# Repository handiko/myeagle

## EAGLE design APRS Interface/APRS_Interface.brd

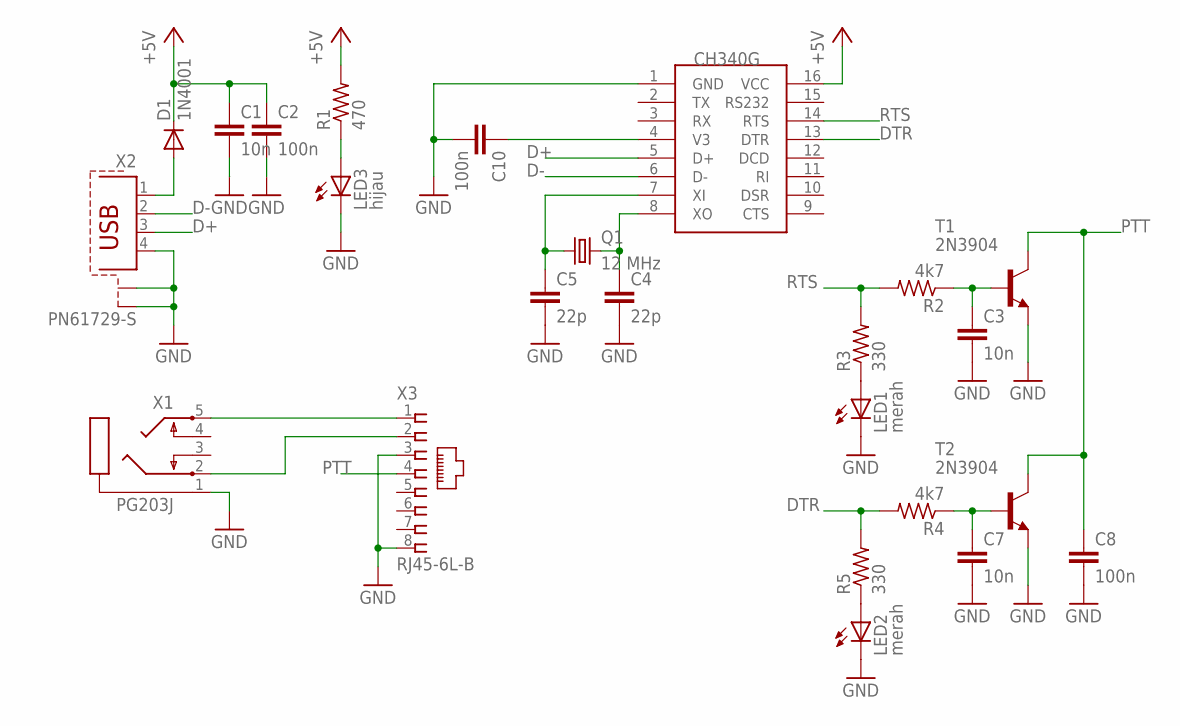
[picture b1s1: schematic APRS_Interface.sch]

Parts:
C1, C3, C7: 10n; C0805K
C2, C8, C10: 100n; C0805K
C4, C5: 22p; C0805K
D1: 1N4001; DO35-7
LED1, LED2: merah; LED3MM
LED3: hijau; LED3MM
Q1: 12 MHz; HC49/S
R1: 470; R0805
R2, R4: 4k7; R0805
R3, R5: 330; R0805
T1, T2: 2N3904; TO92-EBC
U$1: CH340G; SOIC16
X1: PG203J
X2: PN61729-S
X3: RJ45-6L-B; RJ45-NO-SHIELD

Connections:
+5V: C1.1, C2.1, D1.C, R1.2, U$1.16 (VCC)
D+: U$1.5 (D+), X2.3
D-: U$1.6 (D-), X2.2
DTR: R4.2, R5.2, U$1.13 (DTR)
GND: C1.2, C2.2, C3.2, C4.2, C5.2, C7.2, C8.2, C10.2, LED1.K (C), LED2.K (C), LED3.K (C), T1.E, T2.E, U$1.1 (GND), X1.1, X2.4, X2.S1, X2.S2, X3.3, X3.8
unnamed: D1.A, X2.1
unnamed: C4.1, Q1.2, U$1.8 (XO)
unnamed: C5.1, Q1.1, U$1.7 (XI)
unnamed: C10.1, U$1.4 (V3)
unnamed: C3.1, R2.1, T1.B
unnamed: X1.5, X3.1
unnamed: LED1.A, R3.1
unnamed: X1.2, X3.2
unnamed: C7.1, R4.1, T2.B
unnamed: LED3.A, R1.1
unnamed: LED2.A, R5.1
PTT: C8.1, T1.C, T2.C, X3.4
RTS: R2.2, R3.2, U$1.14 (RTS)

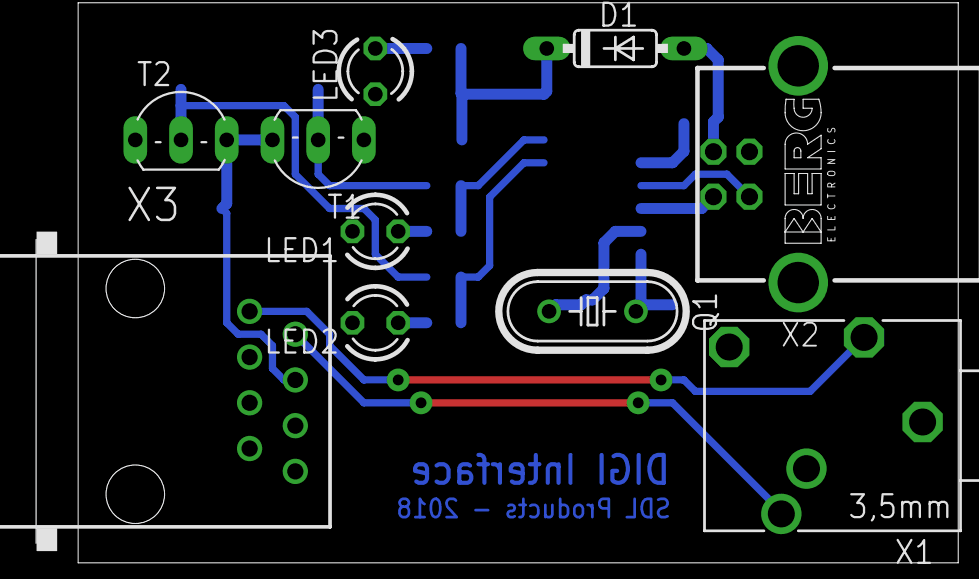
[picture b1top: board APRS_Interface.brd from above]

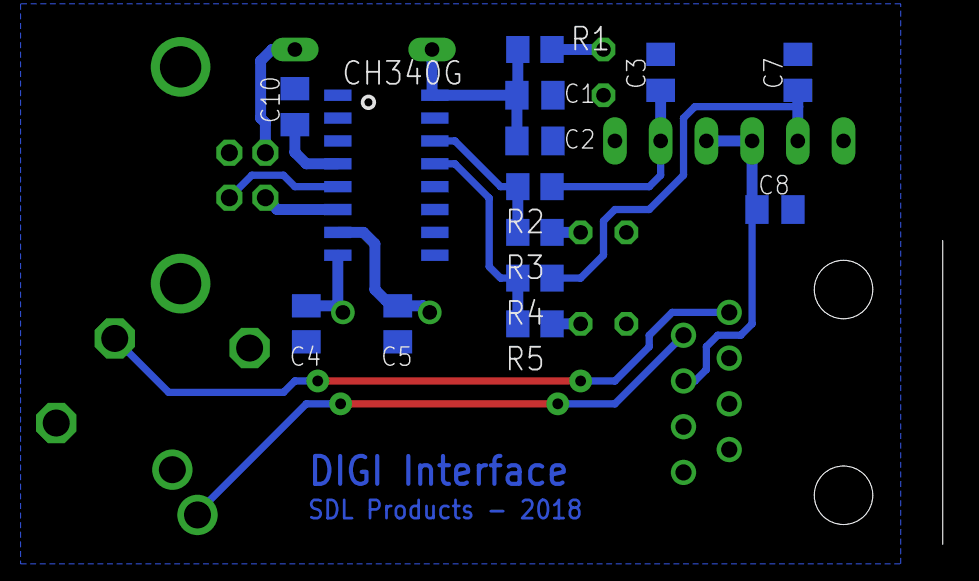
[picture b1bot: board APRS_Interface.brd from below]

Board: 2 copper layers, 24 parts (14 on the bottom side), 18 nets.

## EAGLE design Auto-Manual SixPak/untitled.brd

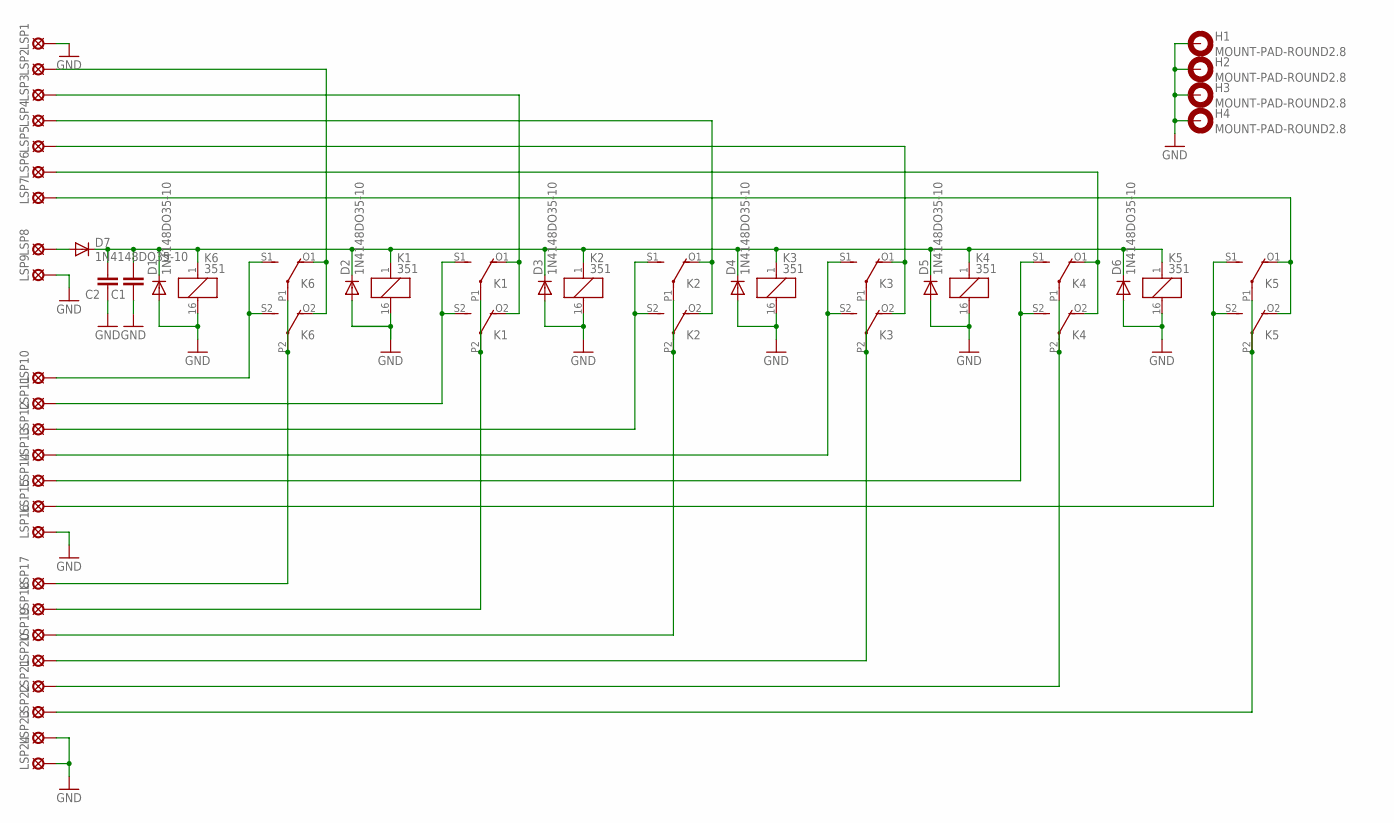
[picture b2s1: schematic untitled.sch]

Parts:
C1, C2: C-EU050-025X075; C050-025X075
D1, D2, D3, D4, D5, D6, D7: 1N4148DO35-10; DO35-10
H1, H2, H3, H4: MOUNT-PAD-ROUND2.8; 2,8-PAD
K1, K2, K3, K4, K5, K6: 351
LSP1, LSP2, LSP3, LSP4, LSP5, LSP6, LSP7, LSP8, LSP9, LSP10, LSP11, LSP12, LSP13, LSP14, LSP15, LSP16, LSP17, LSP18, LSP19, LSP20, LSP21, LSP22, LSP23, LSP24: SE14

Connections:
GND: C1.1, C2.1, D1.A, D2.A, D3.A, D4.A, D5.A, D6.A, H1.B2,8, H2.B2,8, H3.B2,8, H4.B2,8, K2.16 (2), K3.16 (2), K4.16 (2), K5.16 (2), K6.16 (2), LSP1.MP, LSP9.MP, LSP16.MP, LSP23.MP, LSP24.MP
GND1: K1.16 (2)
unnamed: K6.O1 (O), K6.O2 (O), LSP2.MP
unnamed: K6.S1 (S), K6.S2 (S), LSP10.MP
unnamed: K1.O1 (O), K1.O2 (O), LSP3.MP
unnamed: K1.S1 (S), K1.S2 (S), LSP11.MP
unnamed: K2.O1 (O), K2.O2 (O), LSP4.MP
unnamed: K2.S1 (S), K2.S2 (S), LSP12.MP
unnamed: K3.O1 (O), K3.O2 (O), LSP5.MP
unnamed: K3.S1 (S), K3.S2 (S), LSP13.MP
unnamed: K4.O1 (O), K4.O2 (O), LSP6.MP
unnamed: K4.S1 (S), K4.S2 (S), LSP14.MP
unnamed: K5.O1 (O), K5.O2 (O), LSP7.MP
unnamed: K5.S1 (S), K5.S2 (S), LSP15.MP
unnamed: K6.P1, K6.P2, LSP17.MP
unnamed: K1.P1, K1.P2, LSP18.MP
unnamed: K2.P1, K2.P2, LSP19.MP
unnamed: C1.2, C2.2, D1.C, D2.C, D3.C, D4.C, D5.C, D6.C, D7.C, K1.1, K2.1, K3.1, K4.1, K5.1, K6.1
unnamed: K3.P1, K3.P2, LSP20.MP
unnamed: K4.P1, K4.P2, LSP21.MP
unnamed: K5.P1, K5.P2, LSP22.MP
unnamed: D7.A, LSP8.MP

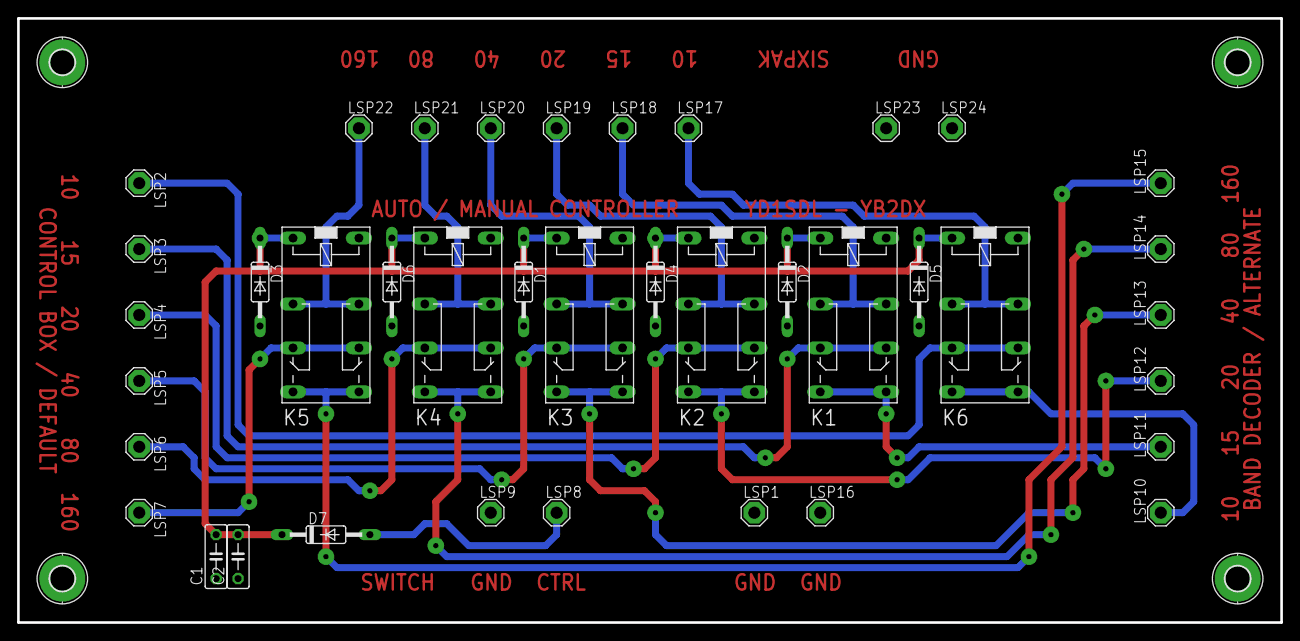
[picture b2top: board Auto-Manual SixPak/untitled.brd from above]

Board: 2 copper layers, 146.1 x 69.8 mm, 43 parts (0 on the bottom side), 21 nets.

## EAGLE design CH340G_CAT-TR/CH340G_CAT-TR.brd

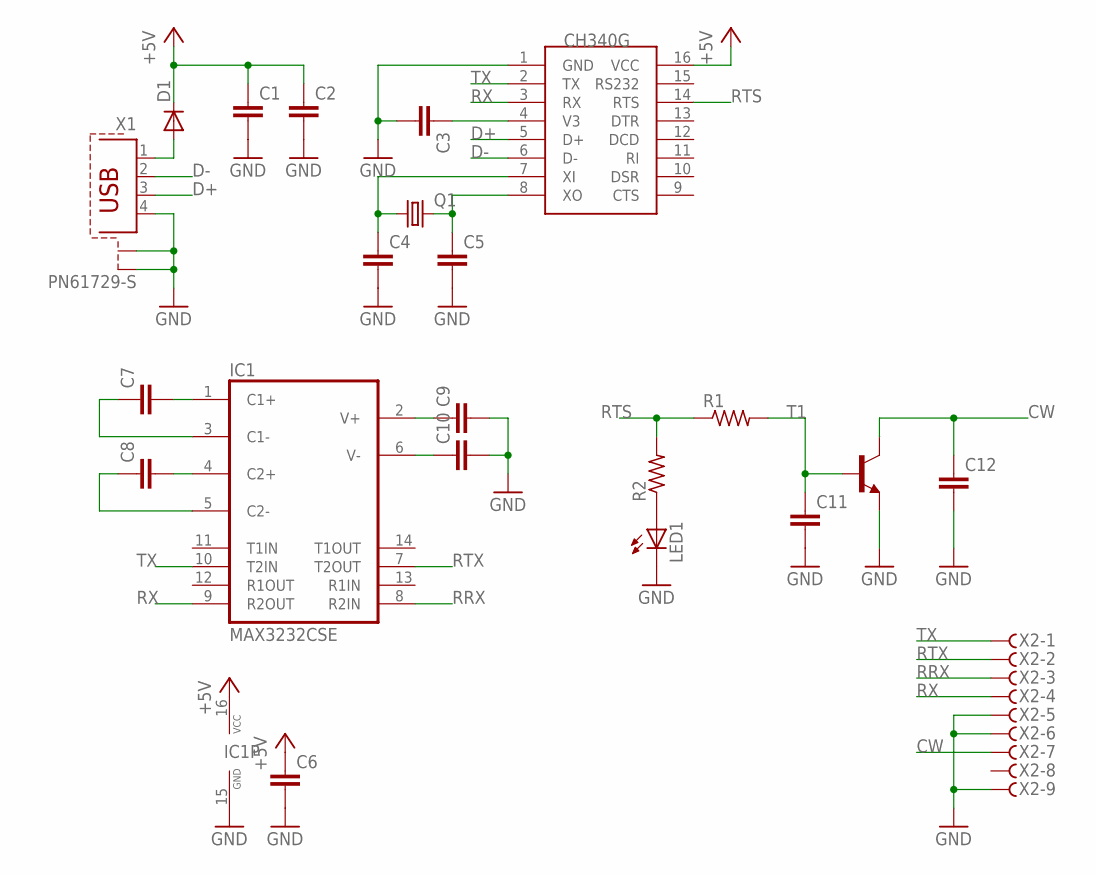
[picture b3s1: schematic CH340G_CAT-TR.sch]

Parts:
C1, C2, C3, C4, C5, C6, C7, C8, C9, C10, C11, C12: C-EUC0805K; C0805K
D1: 1N4148DO35-7; DO35-7
IC1: MAX3232CSE; SO16
LED1: LED3MM
Q1: CRYSTALHC49S; HC49/S
R1, R2: R-US_M0805; M0805
T1: BC548-NPN-TO92-CBE; TO92-CBE
U$1: CH340G; SOIC16
X1: PN61729-S
X2: F09HPS; F09HP

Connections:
+5V: C1.1, C2.1, C6.1, D1.C, IC1.16 (VCC), U$1.16 (VCC)
CW: C12.1, T1.C, X2.7
D+: U$1.5 (D+), X1.3
D-: U$1.6 (D-), X1.2
GND: C1.2, C2.2, C3.2, C4.2, C5.2, C6.2, C9.2, C10.2, C11.2, C12.2, IC1.15 (GND), LED1.K (C), T1.E, U$1.1 (GND), X1.4, X1.S1, X1.S2, X2.5, X2.6, X2.9
unnamed: D1.A, X1.1
unnamed: C4.1, Q1.1, U$1.7 (XI)
unnamed: C5.1, Q1.2, U$1.8 (XO)
unnamed: C10.1, IC1.6 (V-)
unnamed: C3.1, U$1.4 (V3)
unnamed: C9.1, IC1.2 (V+)
unnamed: C8.2, IC1.4 (C2+)
unnamed: C7.2, IC1.1 (C1+)
unnamed: C7.1, IC1.3 (C1-)
unnamed: C8.1, IC1.5 (C2-)
unnamed: C11.1, R1.2, T1.B
unnamed: LED1.A, R2.1
RRX: IC1.8 (R2IN), X2.3
RTS: R1.1, R2.2, U$1.14 (RTS)
RTX: IC1.7 (T2OUT), X2.2
RX: IC1.9 (R2OUT), U$1.3 (RX), X2.4
TX: IC1.10 (T2IN), U$1.2 (TX), X2.1

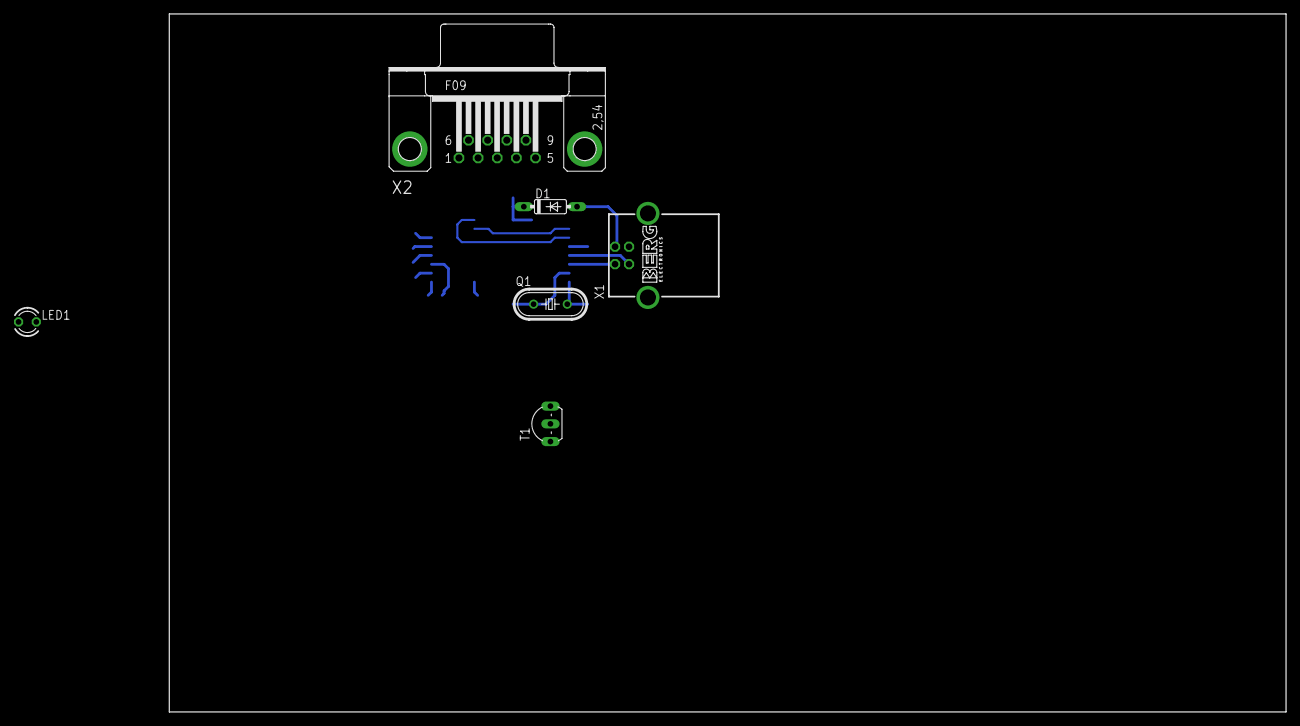
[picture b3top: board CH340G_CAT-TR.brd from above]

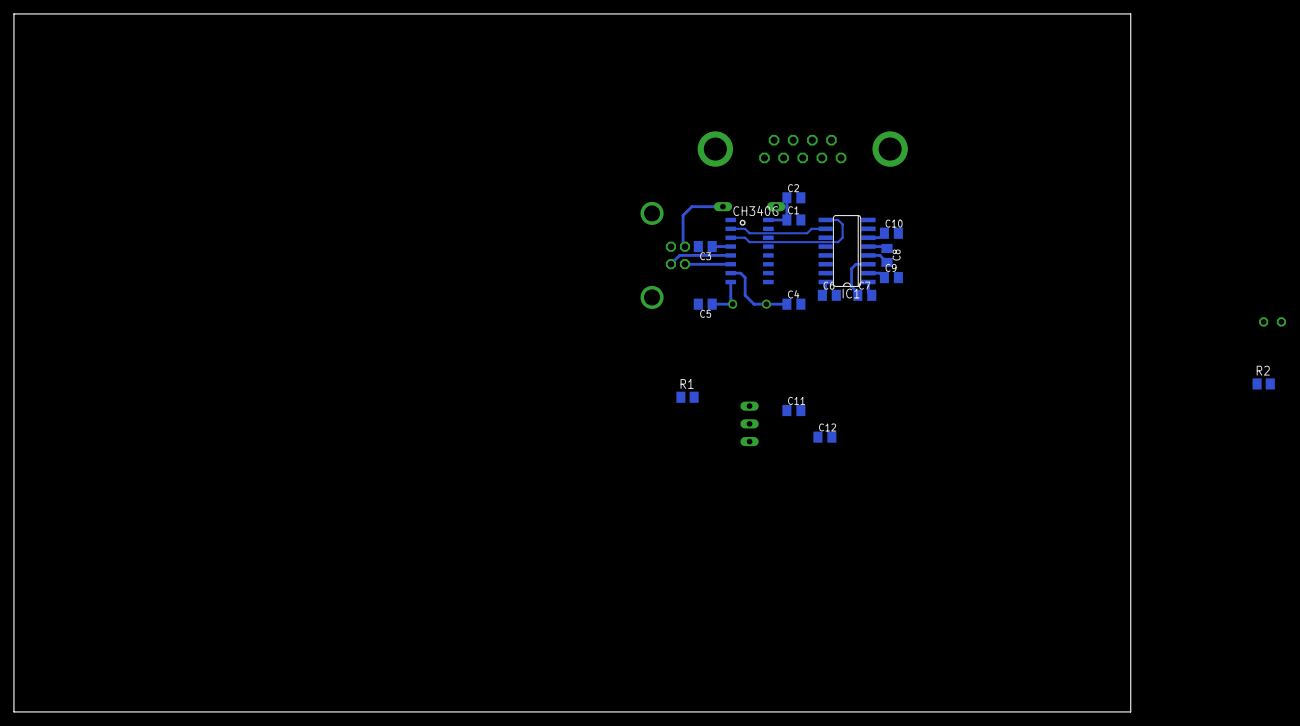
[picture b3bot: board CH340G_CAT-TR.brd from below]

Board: 2 copper layers, 160.0 x 100.0 mm, 22 parts (16 on the bottom side), 22 nets.

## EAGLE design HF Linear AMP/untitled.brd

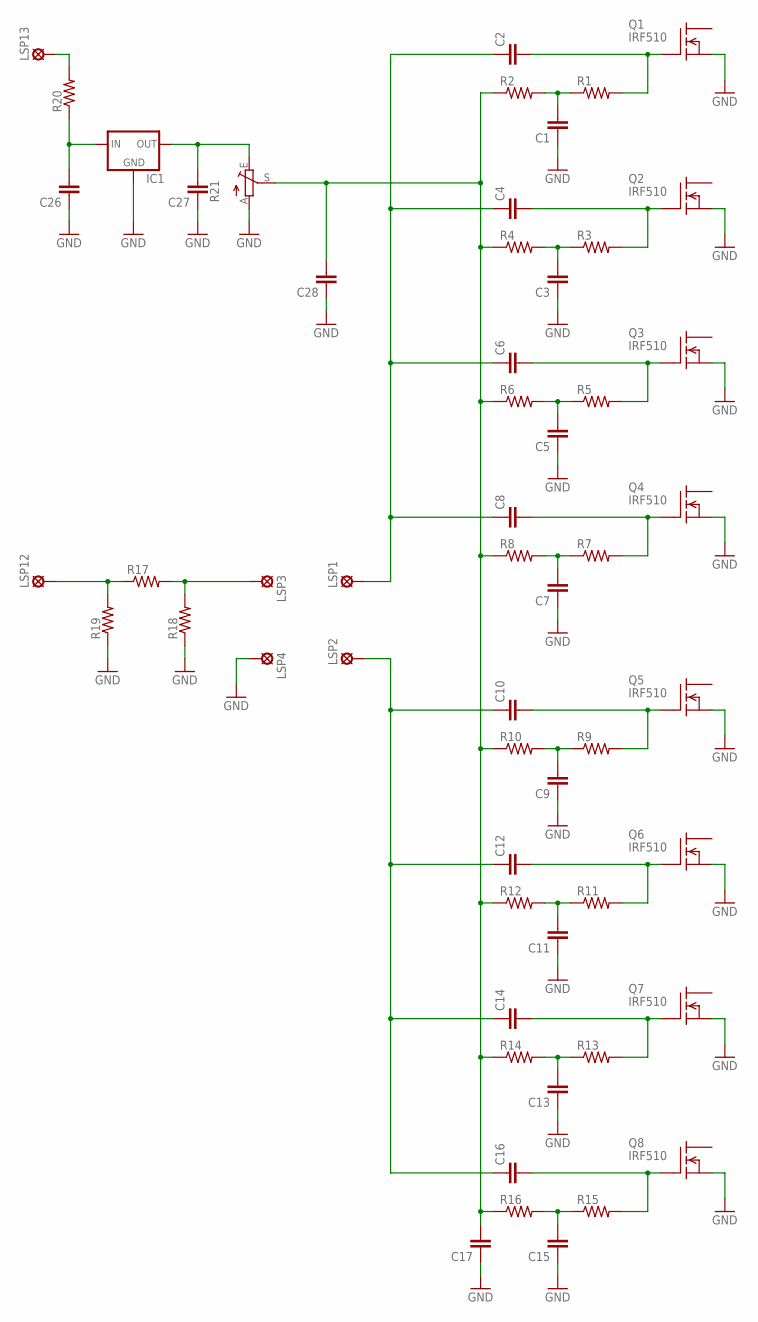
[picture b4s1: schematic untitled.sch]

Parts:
C1, C2, C3, C4, C5, C6, C7, C8, C9, C10, C11, C12, C13, C14, C15, C16, C17, C26, C27, C28: C-EU075-032X103; C075-032X103
IC1: 78XXS
LSP1, LSP2, LSP3, LSP4, LSP12, LSP13: SE14
Q1, Q2, Q3, Q4, Q5, Q6, Q7, Q8: IRF510; TO220
R1, R2, R3, R4, R5, R6, R7, R8, R9, R10, R11, R12, R13, R14, R15, R16, R17, R18, R19, R20: R-US_0309/12; 0309/12
R21: TRIM_EU-CA6V; CA6V

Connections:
GND: C1.1, C3.1, C5.1, C7.1, C9.1, C11.1, C13.1, C15.1, C17.1, C26.1, C27.1, C28.1, IC1.GND, LSP4.MP, Q1.3 (S), Q2.3 (S), Q3.3 (S), Q4.3 (S), Q5.3 (S), Q6.3 (S), Q7.3 (S), Q8.3 (S), R18.1, R19.1, R21.A
unnamed: C2.2, Q1.1 (G), R1.2
unnamed: C1.2, R1.1, R2.2
unnamed: C4.2, Q2.1 (G), R3.2
unnamed: C3.2, R3.1, R4.2
unnamed: C6.2, Q3.1 (G), R5.2
unnamed: C5.2, R5.1, R6.2
unnamed: C8.2, Q4.1 (G), R7.2
unnamed: C7.2, R7.1, R8.2
unnamed: C10.2, Q5.1 (G), R9.2
unnamed: C9.2, R9.1, R10.2
unnamed: C12.2, Q6.1 (G), R11.2
unnamed: C11.2, R11.1, R12.2
unnamed: C14.2, Q7.1 (G), R13.2
unnamed: C13.2, R13.1, R14.2
unnamed: C16.2, Q8.1 (G), R15.2
unnamed: C15.2, R15.1, R16.2
unnamed: C17.2, C28.2, R2.1, R4.1, R6.1, R8.1, R10.1, R12.1, R14.1, R16.1, R21.S
unnamed: C10.1, C12.1, C14.1, C16.1, LSP2.MP
unnamed: C2.1, C4.1, C6.1, C8.1, LSP1.MP
unnamed: LSP3.MP, R17.2, R18.2
unnamed: LSP12.MP, R17.1, R19.2
unnamed: C26.2, IC1.IN, R20.1
unnamed: LSP13.MP, R20.2
unnamed: C27.2, IC1.OUT, R21.E

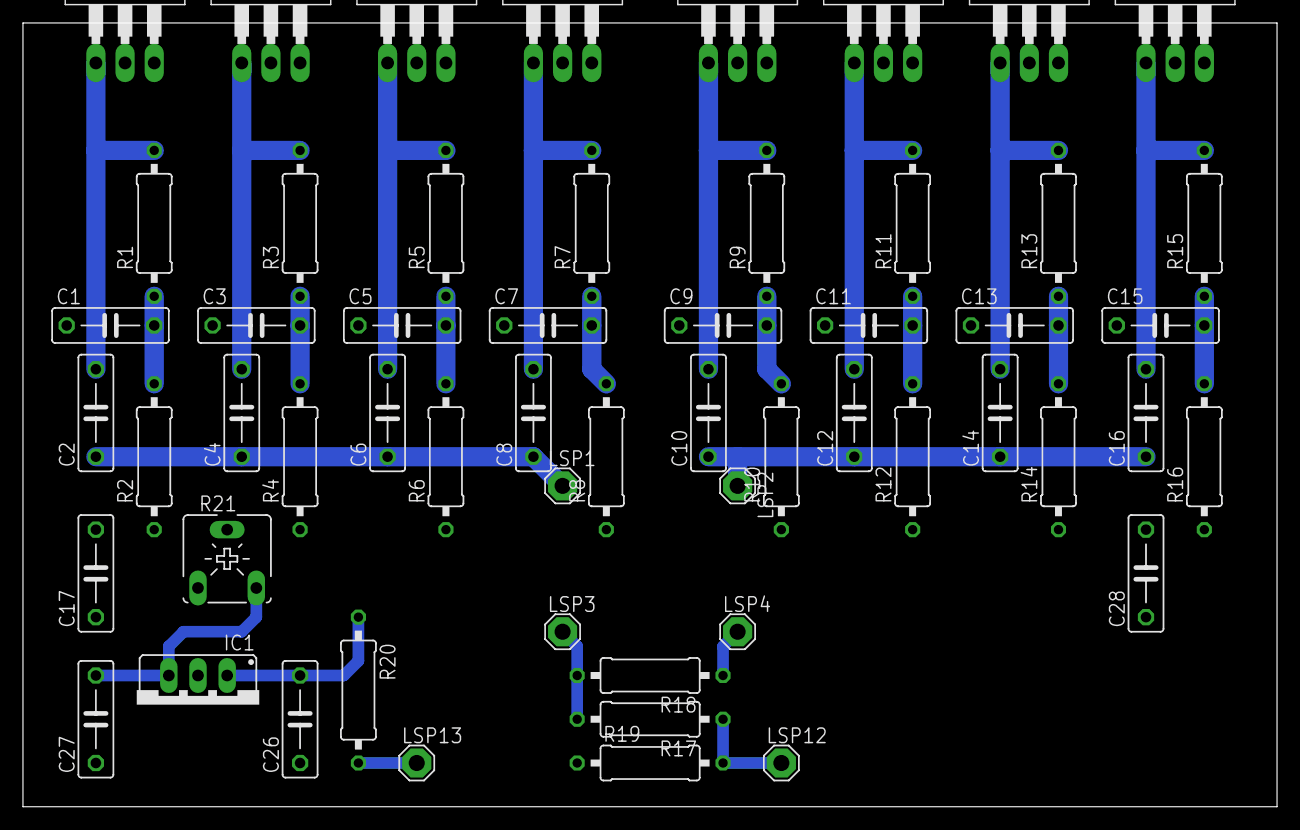
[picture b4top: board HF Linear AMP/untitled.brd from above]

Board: 2 copper layers, 109.2 x 68.2 mm, 56 parts (0 on the bottom side), 25 nets.

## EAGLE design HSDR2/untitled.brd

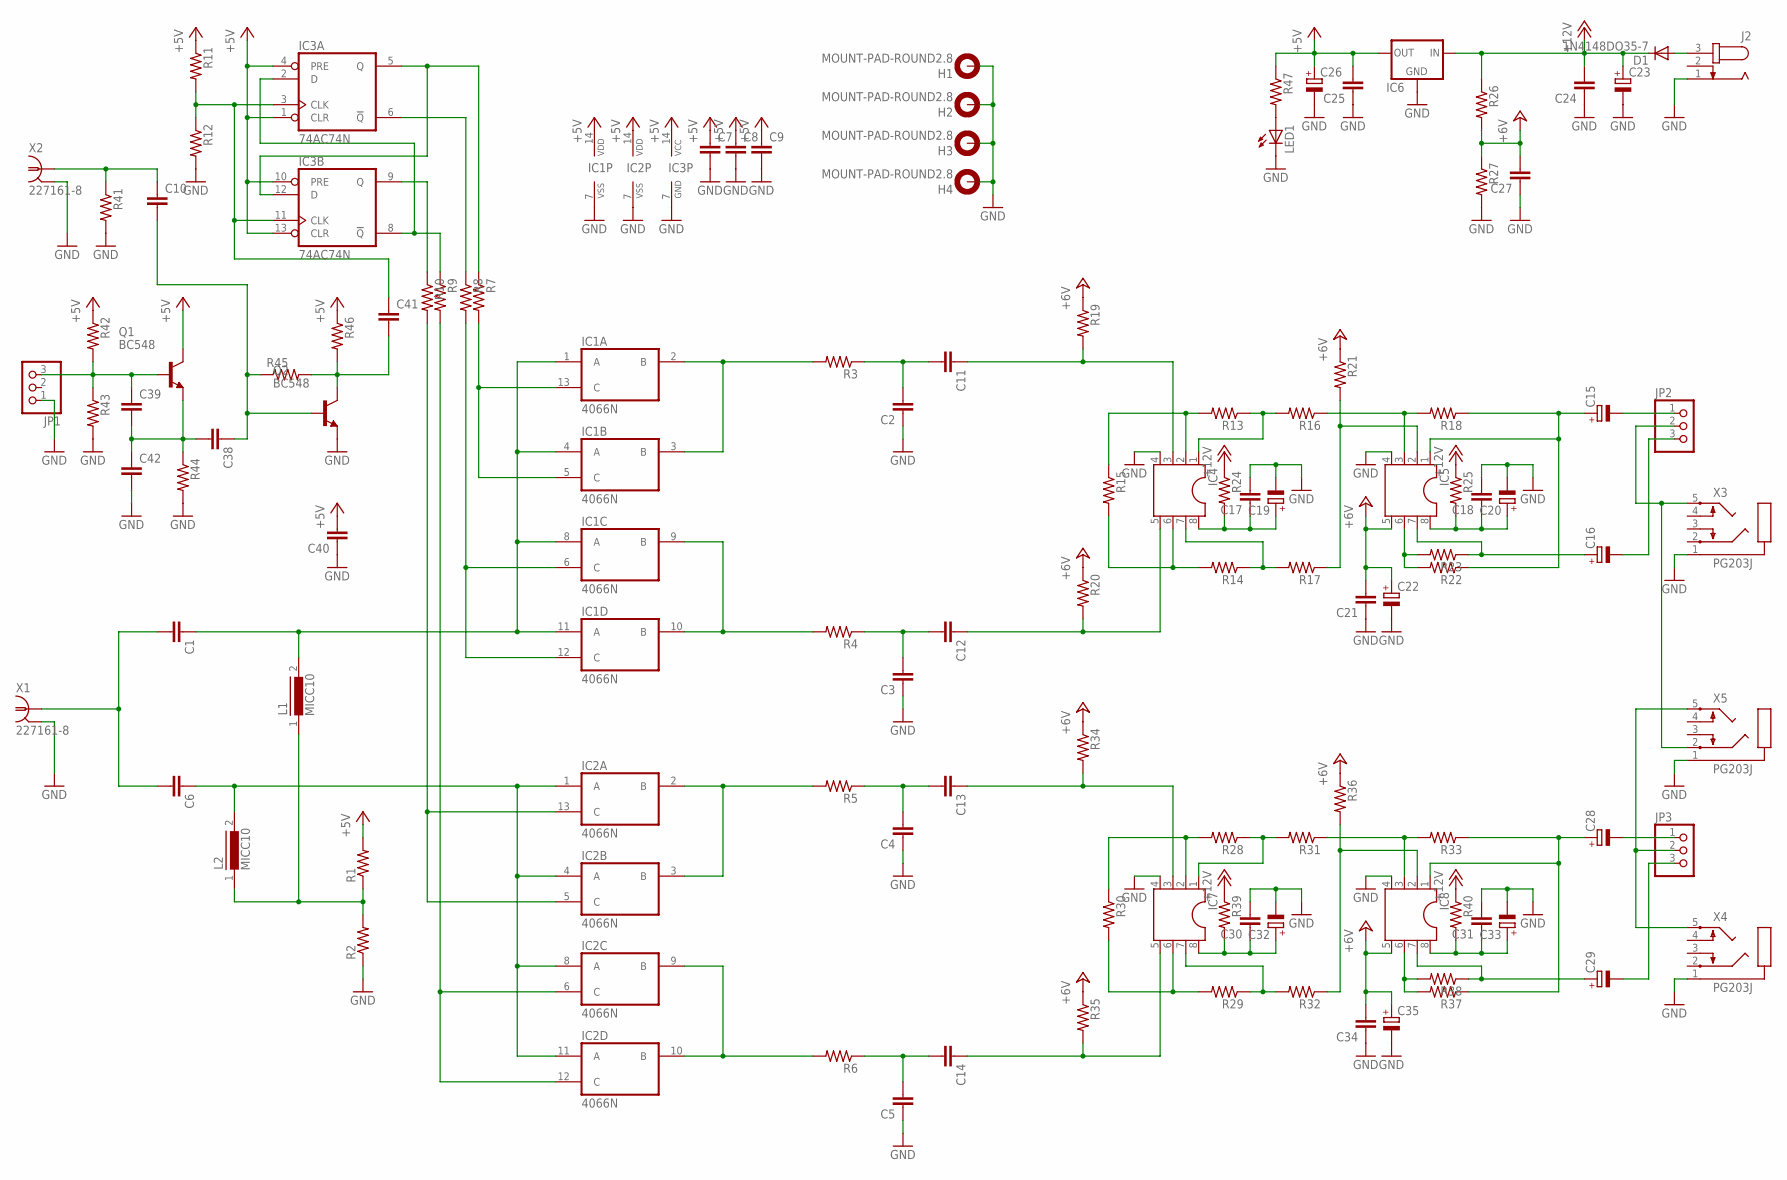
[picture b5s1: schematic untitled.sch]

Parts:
C1, C2, C3, C4, C5, C6, C7, C8, C9, C10, C11, C12, C13, C14, C17, C18, C21, C24, C25, C27, C30, C31, C34, C38, C40: C-EU050-025X075; C050-025X075
C15, C16, C19, C20, C22, C23, C26, C28, C29, C32, C33, C35: CPOL-EUE5-6; E5-6
C39, C42: C-EU025-025X050; C025-025X050
C41: C-EU075-032X103; C075-032X103
D1: 1N4148DO35-7; DO35-7
H1, H2, H3, H4: MOUNT-PAD-ROUND2.8; 2,8-PAD
IC1, IC2: 4066N; DIL14
IC3: 74AC74N; DIL14
IC4, IC5, IC7, IC8: DIL8; DIL08
IC6: 78XXS
J2: JACK-PLUG0; SPC4077
JP1, JP2, JP3: PINHD-1X3; 1X03
L1, L2: MICC10
LED1: LED3MM
Q1, Q2: BC548; TO92-EBC
R1, R2, R3, R4, R5, R6, R7, R8, R9, R10, R11, R12, R13, R14, R15, R16, R17, R18, R19, R20, R21, R22, R23, R24, R25, R26, R27, R28, R29, R30, R31, R32, R33, R34, R35, R36, R37, R38, R39, R40, R41, R42, R43, R44, R45, R46, R47: R-US_0207/7; 0207/7
X1, X2: 227161-8; AMP_227161
X3, X4, X5: PG203J

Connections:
+5V: C7.1, C8.1, C9.1, C25.2, C26.+, C40.2, IC1.14 (VDD), IC2.14 (VDD), IC3.1 (CLR), IC3.4 (PRE), IC3.10 (PRE), IC3.13 (CLR), IC3.14 (VCC), IC6.OUT, Q1.C, R1.2, R11.1, R42.1, R46.1, R47.1
+12V: C23.+, C24.2, D1.C, IC6.IN, R24.1, R25.1, R26.1, R39.1, R40.1
+24V: C21.2, C22.+, C27.2, C34.2, C35.+, IC5.5, IC8.5, R19.1, R20.1, R21.1, R26.2, R27.1, R34.1, R35.1, R36.1
GND: C2.1, C3.1, C4.1, C5.1, C7.2, C8.2, C9.2, C17.2, C18.2, C19.-, C20.-, C21.1, C22.-, C23.-, C24.1, C25.1, C26.-, C27.1, C30.2, C31.2, C32.-, C33.-, C34.1, C35.-, C40.1, C42.2, H1.B2,8, H2.B2,8, H3.B2,8, H4.B2,8, IC1.7 (VSS), IC2.7 (VSS), IC3.7 (GND), IC4.4, IC5.4, IC6.GND, IC7.4, IC8.4, J2.1, JP1.1, LED1.K (C), Q2.E, R2.1, R12.2, R27.2, R41.2, R43.2, R44.2, X1.2, X2.2, X3.1, X4.1, X5.1
unnamed: L1.1, L2.1, R1.1, R2.2
unnamed: C1.2, C6.2, X1.1
unnamed: C1.1, IC1.1 (A), IC1.4 (A), IC1.8 (A), IC1.11 (A), L1.2
unnamed: C6.1, IC2.1 (A), IC2.4 (A), IC2.8 (A), IC2.11 (A), L2.2
unnamed: IC1.9 (B), IC1.10 (B), R4.2
unnamed: IC1.2 (B), IC1.3 (B), R3.2
unnamed: IC2.2 (B), IC2.3 (B), R5.2
unnamed: IC2.9 (B), IC2.10 (B), R6.2
unnamed: IC1.5 (C), IC1.13 (C), R7.2
unnamed: IC1.6 (C), IC1.12 (C), R8.2
unnamed: IC2.5 (C), IC2.13 (C), R10.2
unnamed: IC2.6 (C), IC2.12 (C), R9.2
unnamed: C2.2, C11.2, R3.1
unnamed: C3.2, C12.2, R4.1
unnamed: C4.2, C13.2, R5.1
unnamed: C5.2, C14.2, R6.1
unnamed: IC3.2 (D), IC3.8 (!Q), R9.1
unnamed: IC3.6 (!Q), R8.1
unnamed: IC3.5 (Q), IC3.12 (D), R7.1
unnamed: IC3.9 (Q), R10.1
unnamed: C41.1, IC3.3 (CLK), IC3.11 (CLK), R11.2, R12.1
unnamed: C11.1, IC4.3, R19.2
unnamed: C12.1, IC4.5, R20.2
unnamed: IC4.2, R13.2, R15.1
unnamed: IC4.6, R14.2, R15.2
unnamed: IC4.7, R14.1, R17.2
unnamed: IC4.1, R13.1, R16.2
unnamed: IC5.2, R17.1, R21.2
unnamed: C15.+, IC5.1, R18.1, R22.1
unnamed: IC5.3, R16.1, R18.2
unnamed: IC5.6, R22.2, R23.2
unnamed: C16.+, IC5.7, R23.1
unnamed: C17.1, C19.+, IC4.8, R24.2
unnamed: C18.1, C20.+, IC5.8, R25.2
unnamed: D1.A, J2.3
unnamed: C10.1, R41.1, X2.1
unnamed: C15.-, JP2.1
unnamed: C13.1, IC7.3, R34.2
unnamed: C14.1, IC7.5, R35.2
unnamed: IC7.2, R28.2, R30.1
unnamed: IC7.6, R29.2, R30.2
unnamed: IC7.7, R29.1, R32.2
unnamed: IC7.1, R28.1, R31.2
unnamed: IC8.3, R31.1, R33.2
unnamed: IC8.2, R32.1, R36.2
unnamed: C28.+, IC8.1, R33.1, R37.1
unnamed: IC8.6, R37.2, R38.2
unnamed: C29.+, IC8.7, R38.1
unnamed: C30.1, C32.+, IC7.8, R39.2
unnamed: C31.1, C33.+, IC8.8, R40.2
unnamed: C16.-, JP2.3
unnamed: C28.-, JP3.1
unnamed: C29.-, JP3.3
unnamed: C39.1, JP1.3, Q1.B, R42.2, R43.1
unnamed: C38.2, C39.2, C42.1, Q1.E, R44.1
unnamed: JP2.2, X3.5, X5.2
unnamed: C41.2, Q2.C, R45.2, R46.2
unnamed: C10.2, C38.1, Q2.B, R45.1
unnamed: LED1.A, R47.2
unnamed: JP3.2, X4.5, X5.5

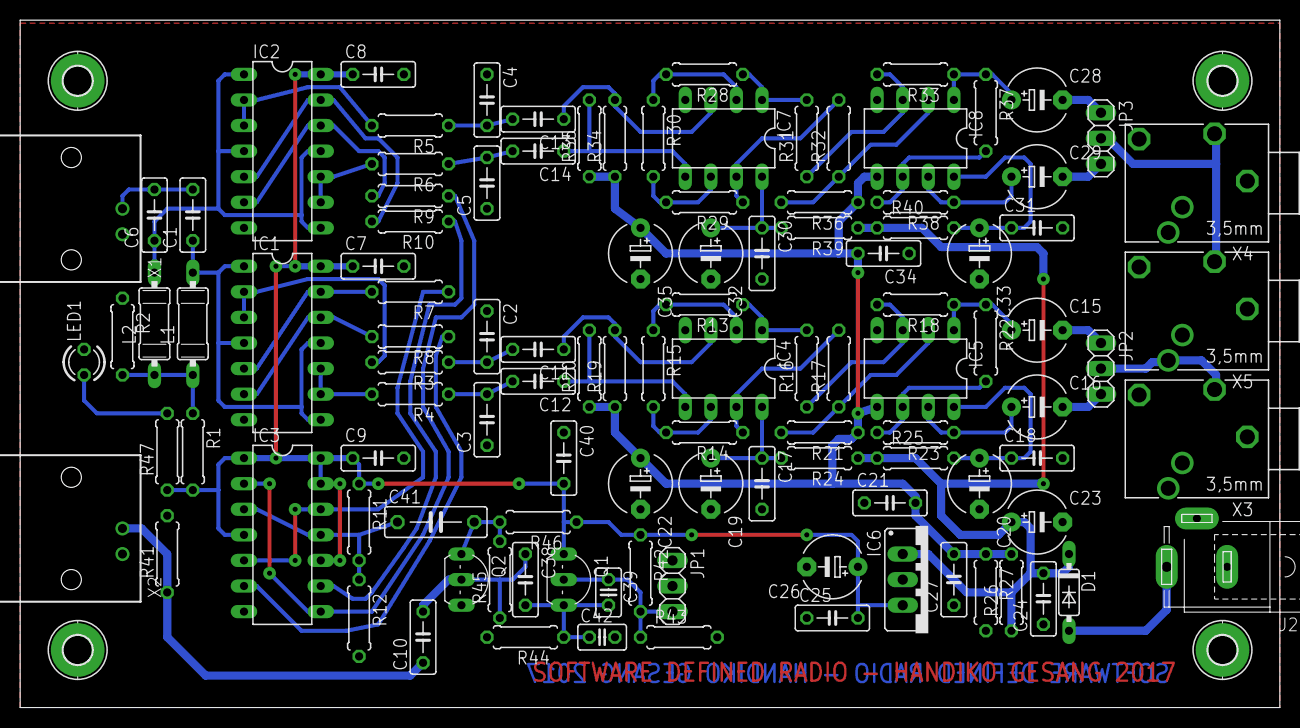
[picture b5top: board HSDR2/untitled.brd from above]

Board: 2 copper layers, 125.1 x 68.2 mm, 114 parts (0 on the bottom side), 64 nets.
